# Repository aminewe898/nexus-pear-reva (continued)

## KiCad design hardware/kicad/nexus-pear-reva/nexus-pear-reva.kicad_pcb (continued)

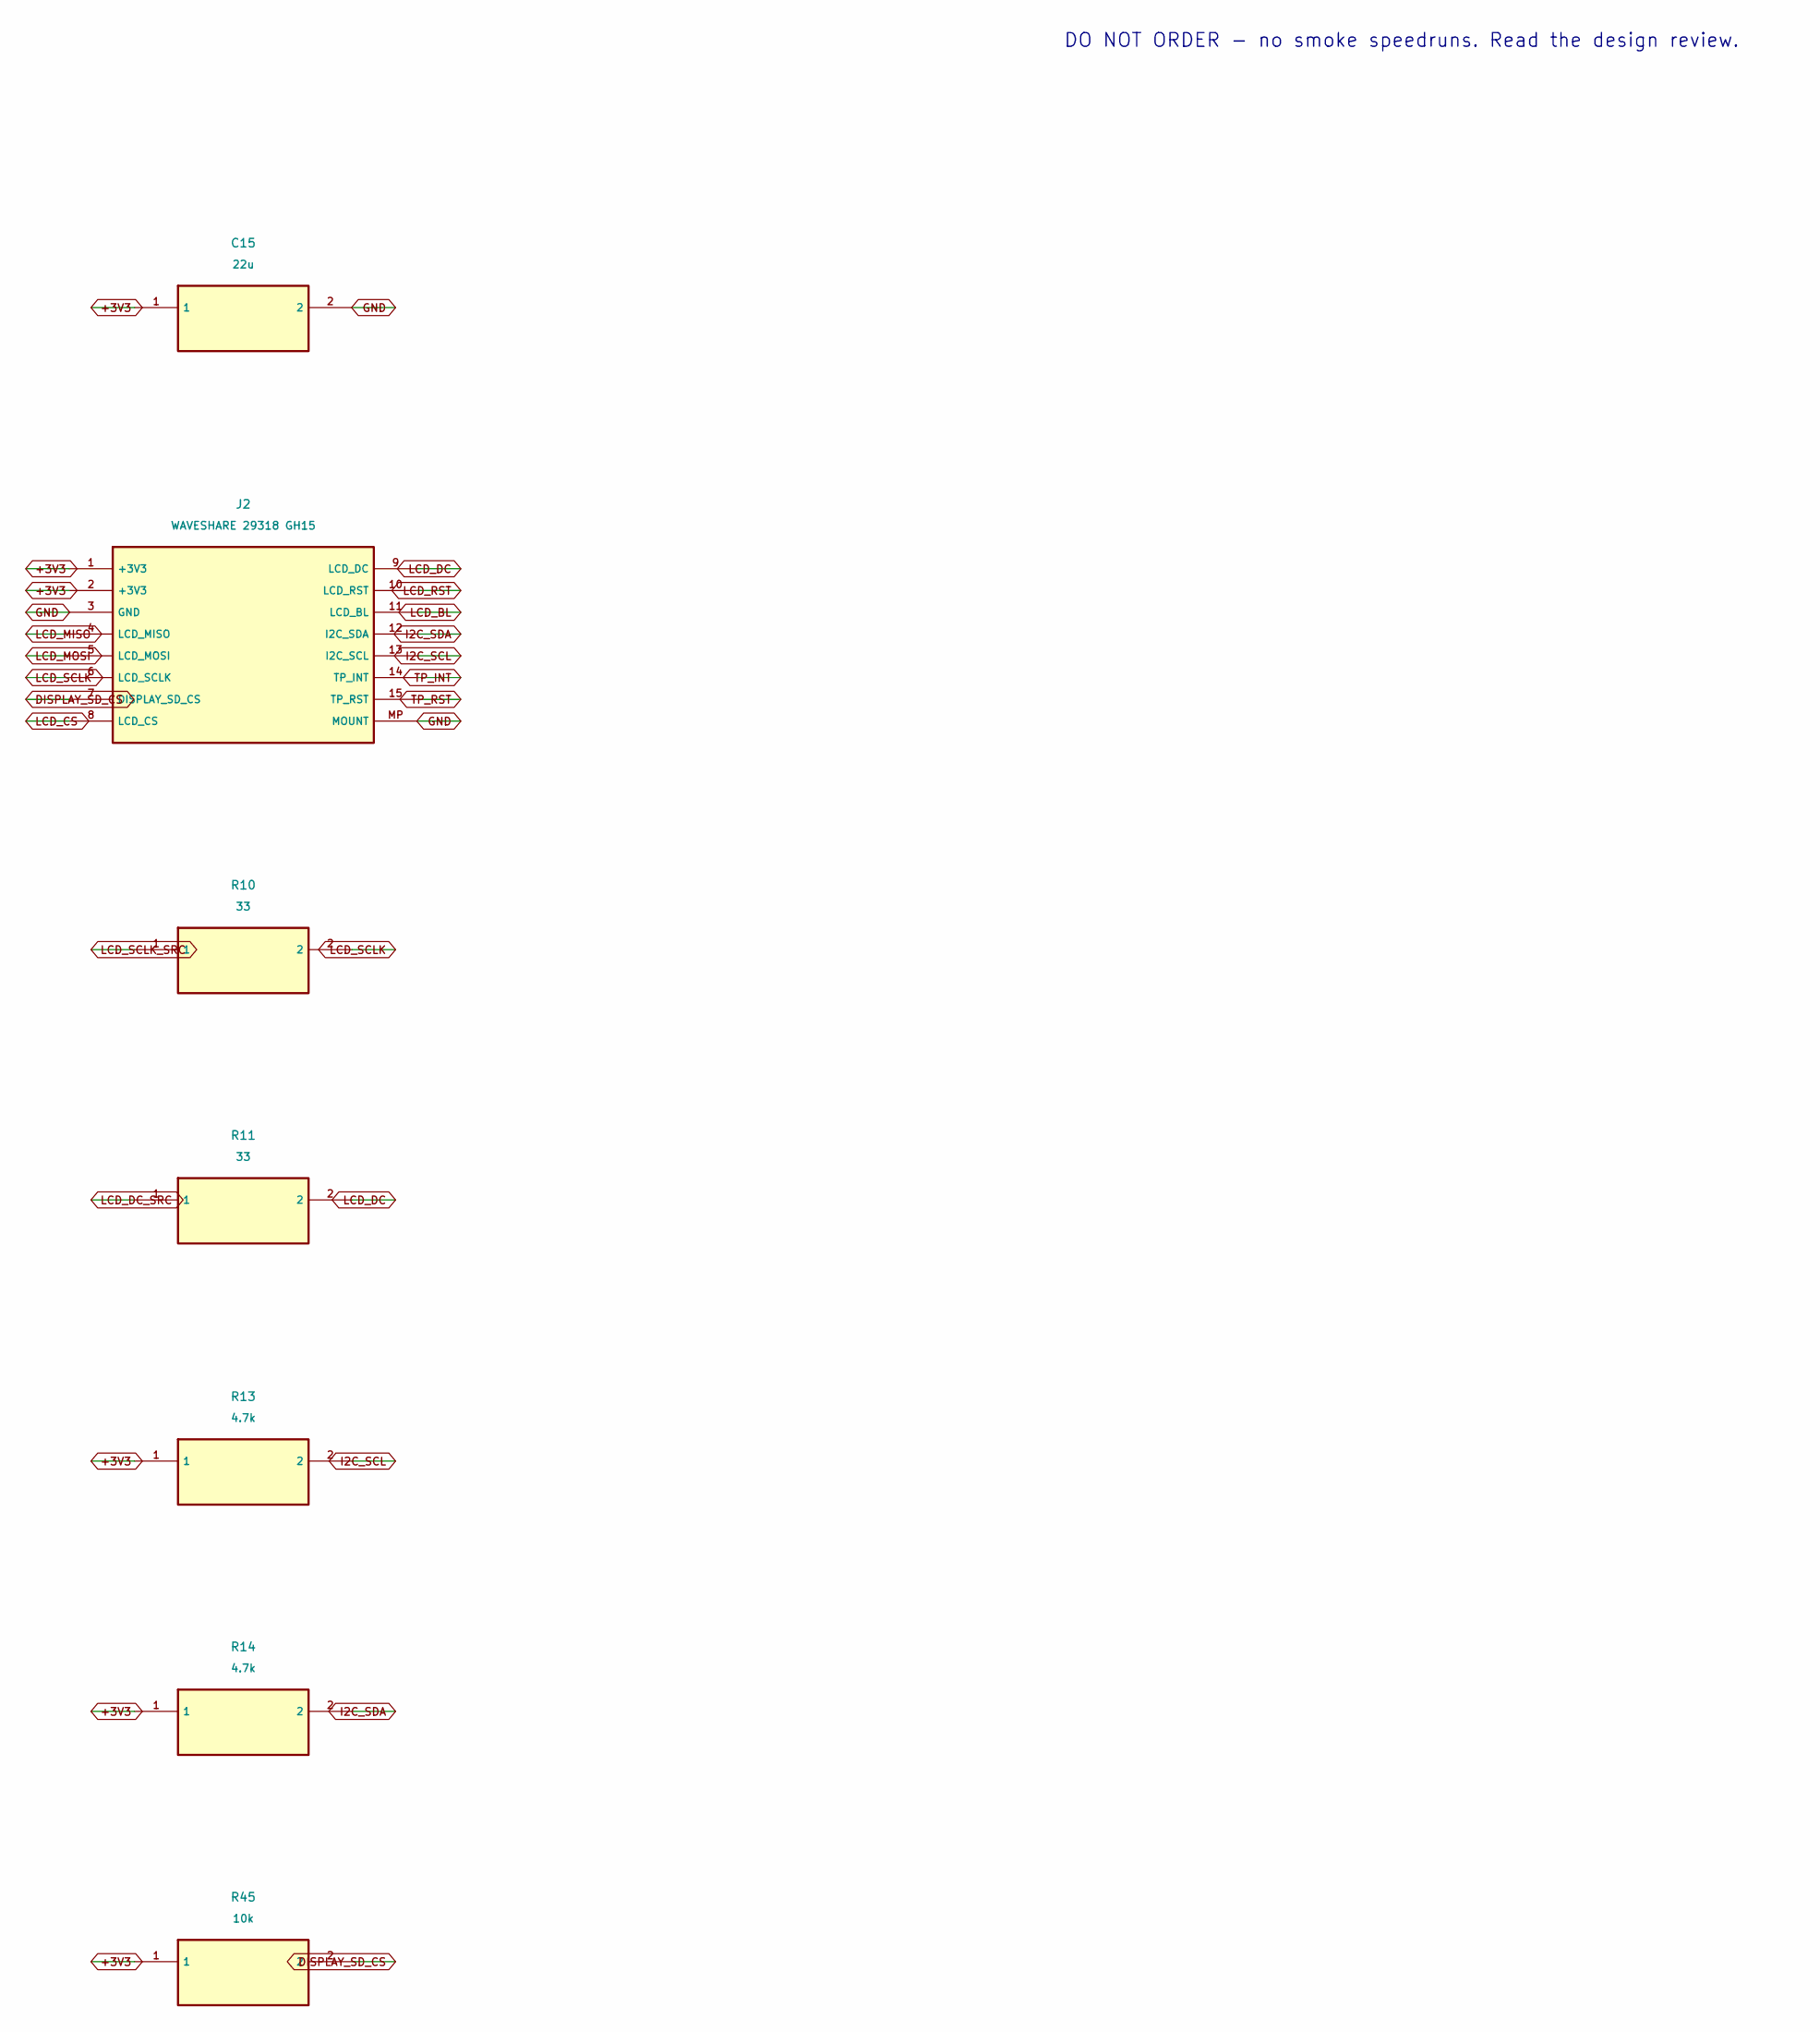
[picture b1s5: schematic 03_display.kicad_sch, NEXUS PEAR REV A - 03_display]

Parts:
C15: 22u; C_1206_3216Metric; MPN GRM31CR61A226KE19L
J2: WAVESHARE 29318 GH15; JST_GH_SM15B-GHS-TB_1x15-1MP_P1.25mm_Horizontal; MPN SM15B-GHS-TB(LF)(SN)
R10, R11: 33; R_0805_2012Metric; MPN RC0805FR-0733RL
R13, R14: 4.7k; R_0805_2012Metric; MPN RC0805FR-074K7L
R45: 10k; R_0805_2012Metric; MPN RC0805FR-0710KL

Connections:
+3V3: C15.1, J2.1 (+3V3), J2.2 (+3V3), R13.1, R14.1, R45.1; also elsewhere on the board
DISPLAY_SD_CS: J2.7 (DISPLAY_SD_CS), R45.2
GND: C15.2, J2.3 (GND), J2.MP (MOUNT); also elsewhere on the board
I2C_SCL: J2.13 (I2C_SCL), R13.2; also elsewhere on the board
I2C_SDA: J2.12 (I2C_SDA), R14.2; also elsewhere on the board
LCD_BL: J2.11 (LCD_BL); also elsewhere on the board
LCD_CS: J2.8 (LCD_CS); also elsewhere on the board
LCD_DC: J2.9 (LCD_DC), R11.2
LCD_DC_SRC: R11.1; also elsewhere on the board
LCD_MISO: J2.4 (LCD_MISO); also elsewhere on the board
LCD_MOSI: J2.5 (LCD_MOSI); also elsewhere on the board
LCD_RST: J2.10 (LCD_RST); also elsewhere on the board
LCD_SCLK: J2.6 (LCD_SCLK), R10.2
LCD_SCLK_SRC: R10.1; also elsewhere on the board
TP_INT: J2.14 (TP_INT); also elsewhere on the board
TP_RST: J2.15 (TP_RST); also elsewhere on the board

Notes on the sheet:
DO NOT ORDER - no smoke speedruns. Read the design review.

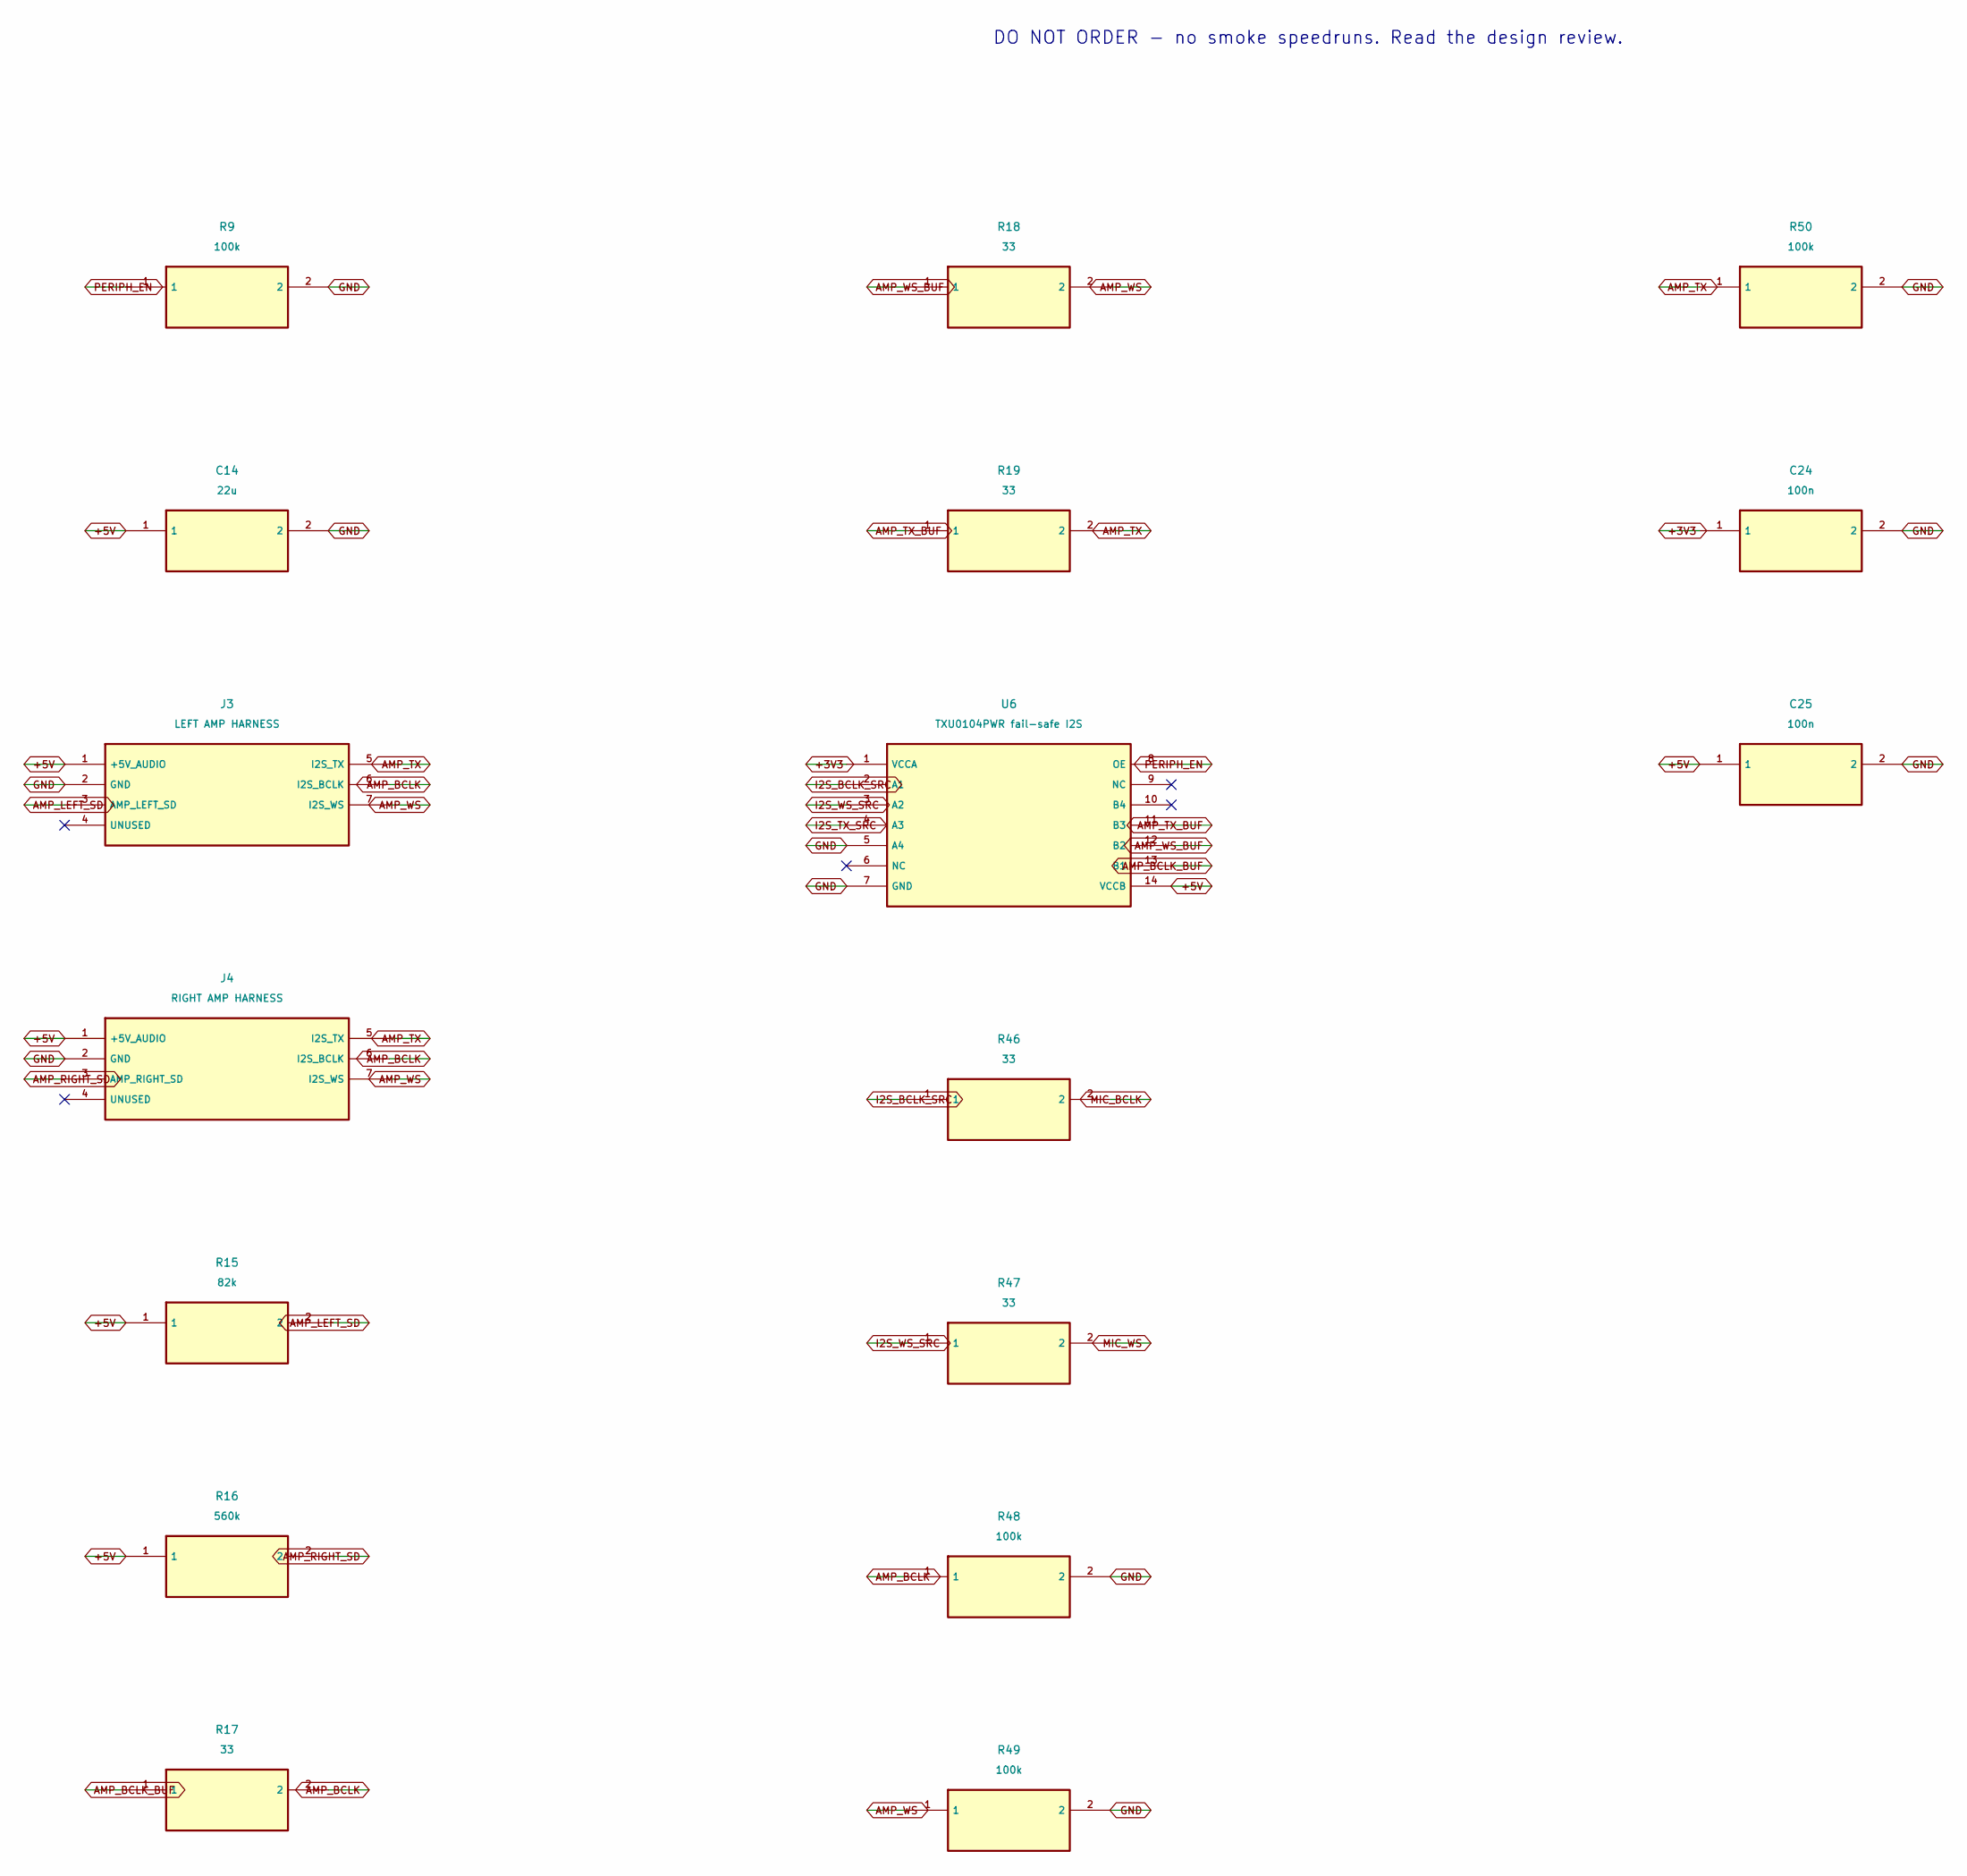
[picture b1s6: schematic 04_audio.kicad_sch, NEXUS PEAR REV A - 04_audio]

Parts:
C14: 22u; C_1206_3216Metric; MPN GRM31CR61A226KE19L
C24, C25: 100n; C_0805_2012Metric; MPN GRM21BR71H104KA01L
J3: LEFT AMP HARNESS; PinHeader_1x07_P2.54mm_Vertical; MPN TSW-007-07-G-S
J4: RIGHT AMP HARNESS; PinHeader_1x07_P2.54mm_Vertical; MPN TSW-007-07-G-S
R9, R48, R49, R50: 100k; R_0805_2012Metric; MPN RC0805FR-07100KL
R15: 82k; R_0805_2012Metric; MPN RC0805FR-0782KL
R16: 560k; R_0805_2012Metric; MPN RC0805FR-07560KL
R17, R18, R19, R46, R47: 33; R_0805_2012Metric; MPN RC0805FR-0733RL
U6: TXU0104PWR fail-safe I2S; TSSOP-14_4.4x5mm_P0.65mm; MPN TXU0104PWR

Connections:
+3V3: C24.1, U6.1 (VCCA); also elsewhere on the board
+5V: C14.1, C25.1, J3.1 (+5V_AUDIO), J4.1 (+5V_AUDIO), R15.1, R16.1, U6.14 (VCCB); also elsewhere on the board
AMP_BCLK: J3.6 (I2S_BCLK), J4.6 (I2S_BCLK), R17.2, R48.1
AMP_BCLK_BUF: R17.1, U6.13 (B1)
AMP_LEFT_SD: J3.3 (AMP_LEFT_SD), R15.2
AMP_RIGHT_SD: J4.3 (AMP_RIGHT_SD), R16.2
AMP_TX: J3.5 (I2S_TX), J4.5 (I2S_TX), R19.2, R50.1
AMP_TX_BUF: R19.1, U6.11 (B3)
AMP_WS: J3.7 (I2S_WS), J4.7 (I2S_WS), R18.2, R49.1
AMP_WS_BUF: R18.1, U6.12 (B2)
GND: C14.2, C24.2, C25.2, J3.2 (GND), J4.2 (GND), R9.2, R48.2, R49.2, R50.2, U6.5 (A4), U6.7 (GND); also elsewhere on the board
I2S_BCLK_SRC: R46.1, U6.2 (A1); also elsewhere on the board
I2S_TX_SRC: U6.4 (A3); also elsewhere on the board
I2S_WS_SRC: R47.1, U6.3 (A2); also elsewhere on the board
MIC_BCLK: R46.2; also elsewhere on the board
MIC_WS: R47.2; also elsewhere on the board
PERIPH_EN: R9.1, U6.8 (OE); also elsewhere on the board

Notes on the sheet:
DO NOT ORDER - no smoke speedruns. Read the design review.

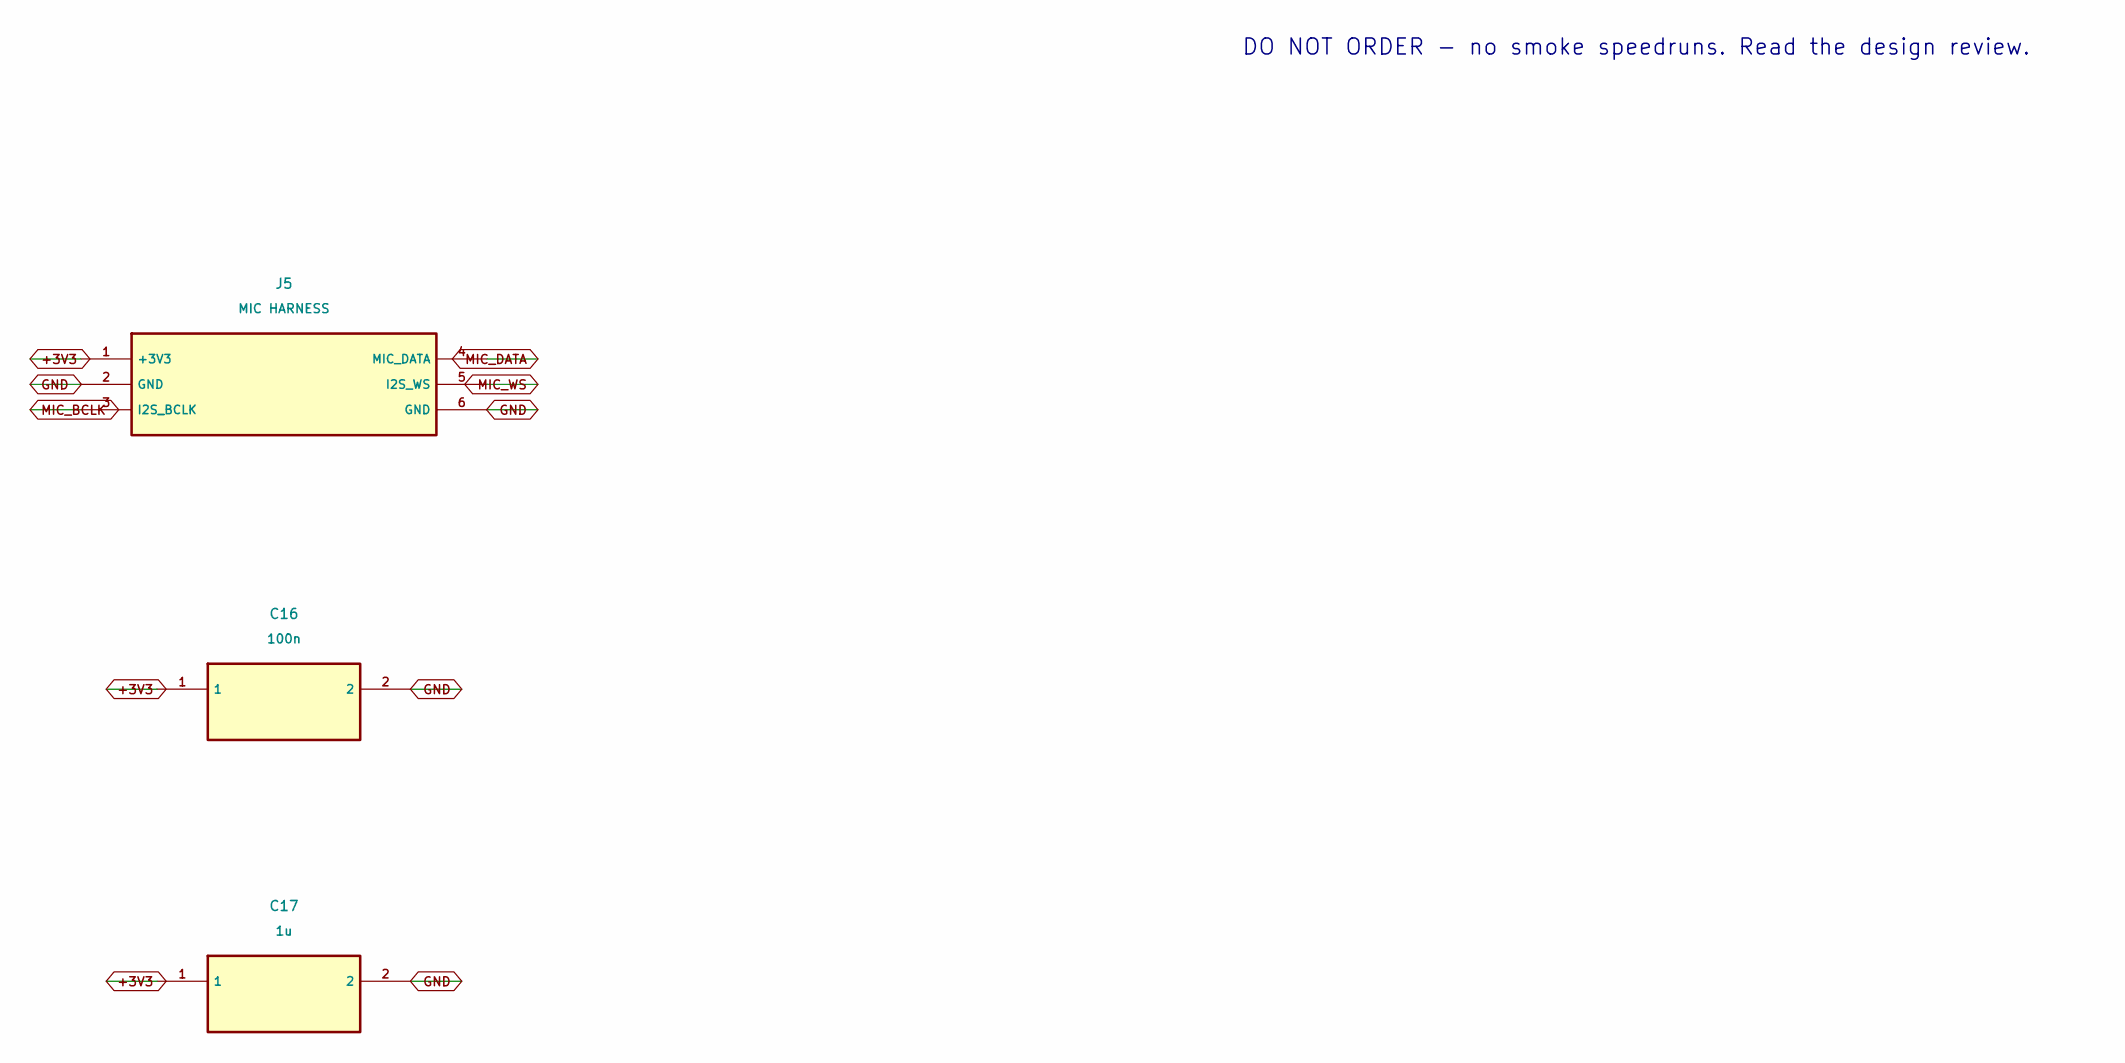
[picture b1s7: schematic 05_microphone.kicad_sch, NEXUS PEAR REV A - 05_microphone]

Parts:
C16: 100n; C_0805_2012Metric; MPN GRM21BR71H104KA01L
C17: 1u; C_0805_2012Metric; MPN GRM21BR71A105KA01L
J5: MIC HARNESS; PinHeader_1x06_P2.54mm_Vertical; MPN TSW-006-07-G-S

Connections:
+3V3: C16.1, C17.1, J5.1 (+3V3); also elsewhere on the board
GND: C16.2, C17.2, J5.2 (GND), J5.6 (GND); also elsewhere on the board
MIC_BCLK: J5.3 (I2S_BCLK); also elsewhere on the board
MIC_DATA: J5.4 (MIC_DATA); also elsewhere on the board
MIC_WS: J5.5 (I2S_WS); also elsewhere on the board

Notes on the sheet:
DO NOT ORDER - no smoke speedruns. Read the design review.

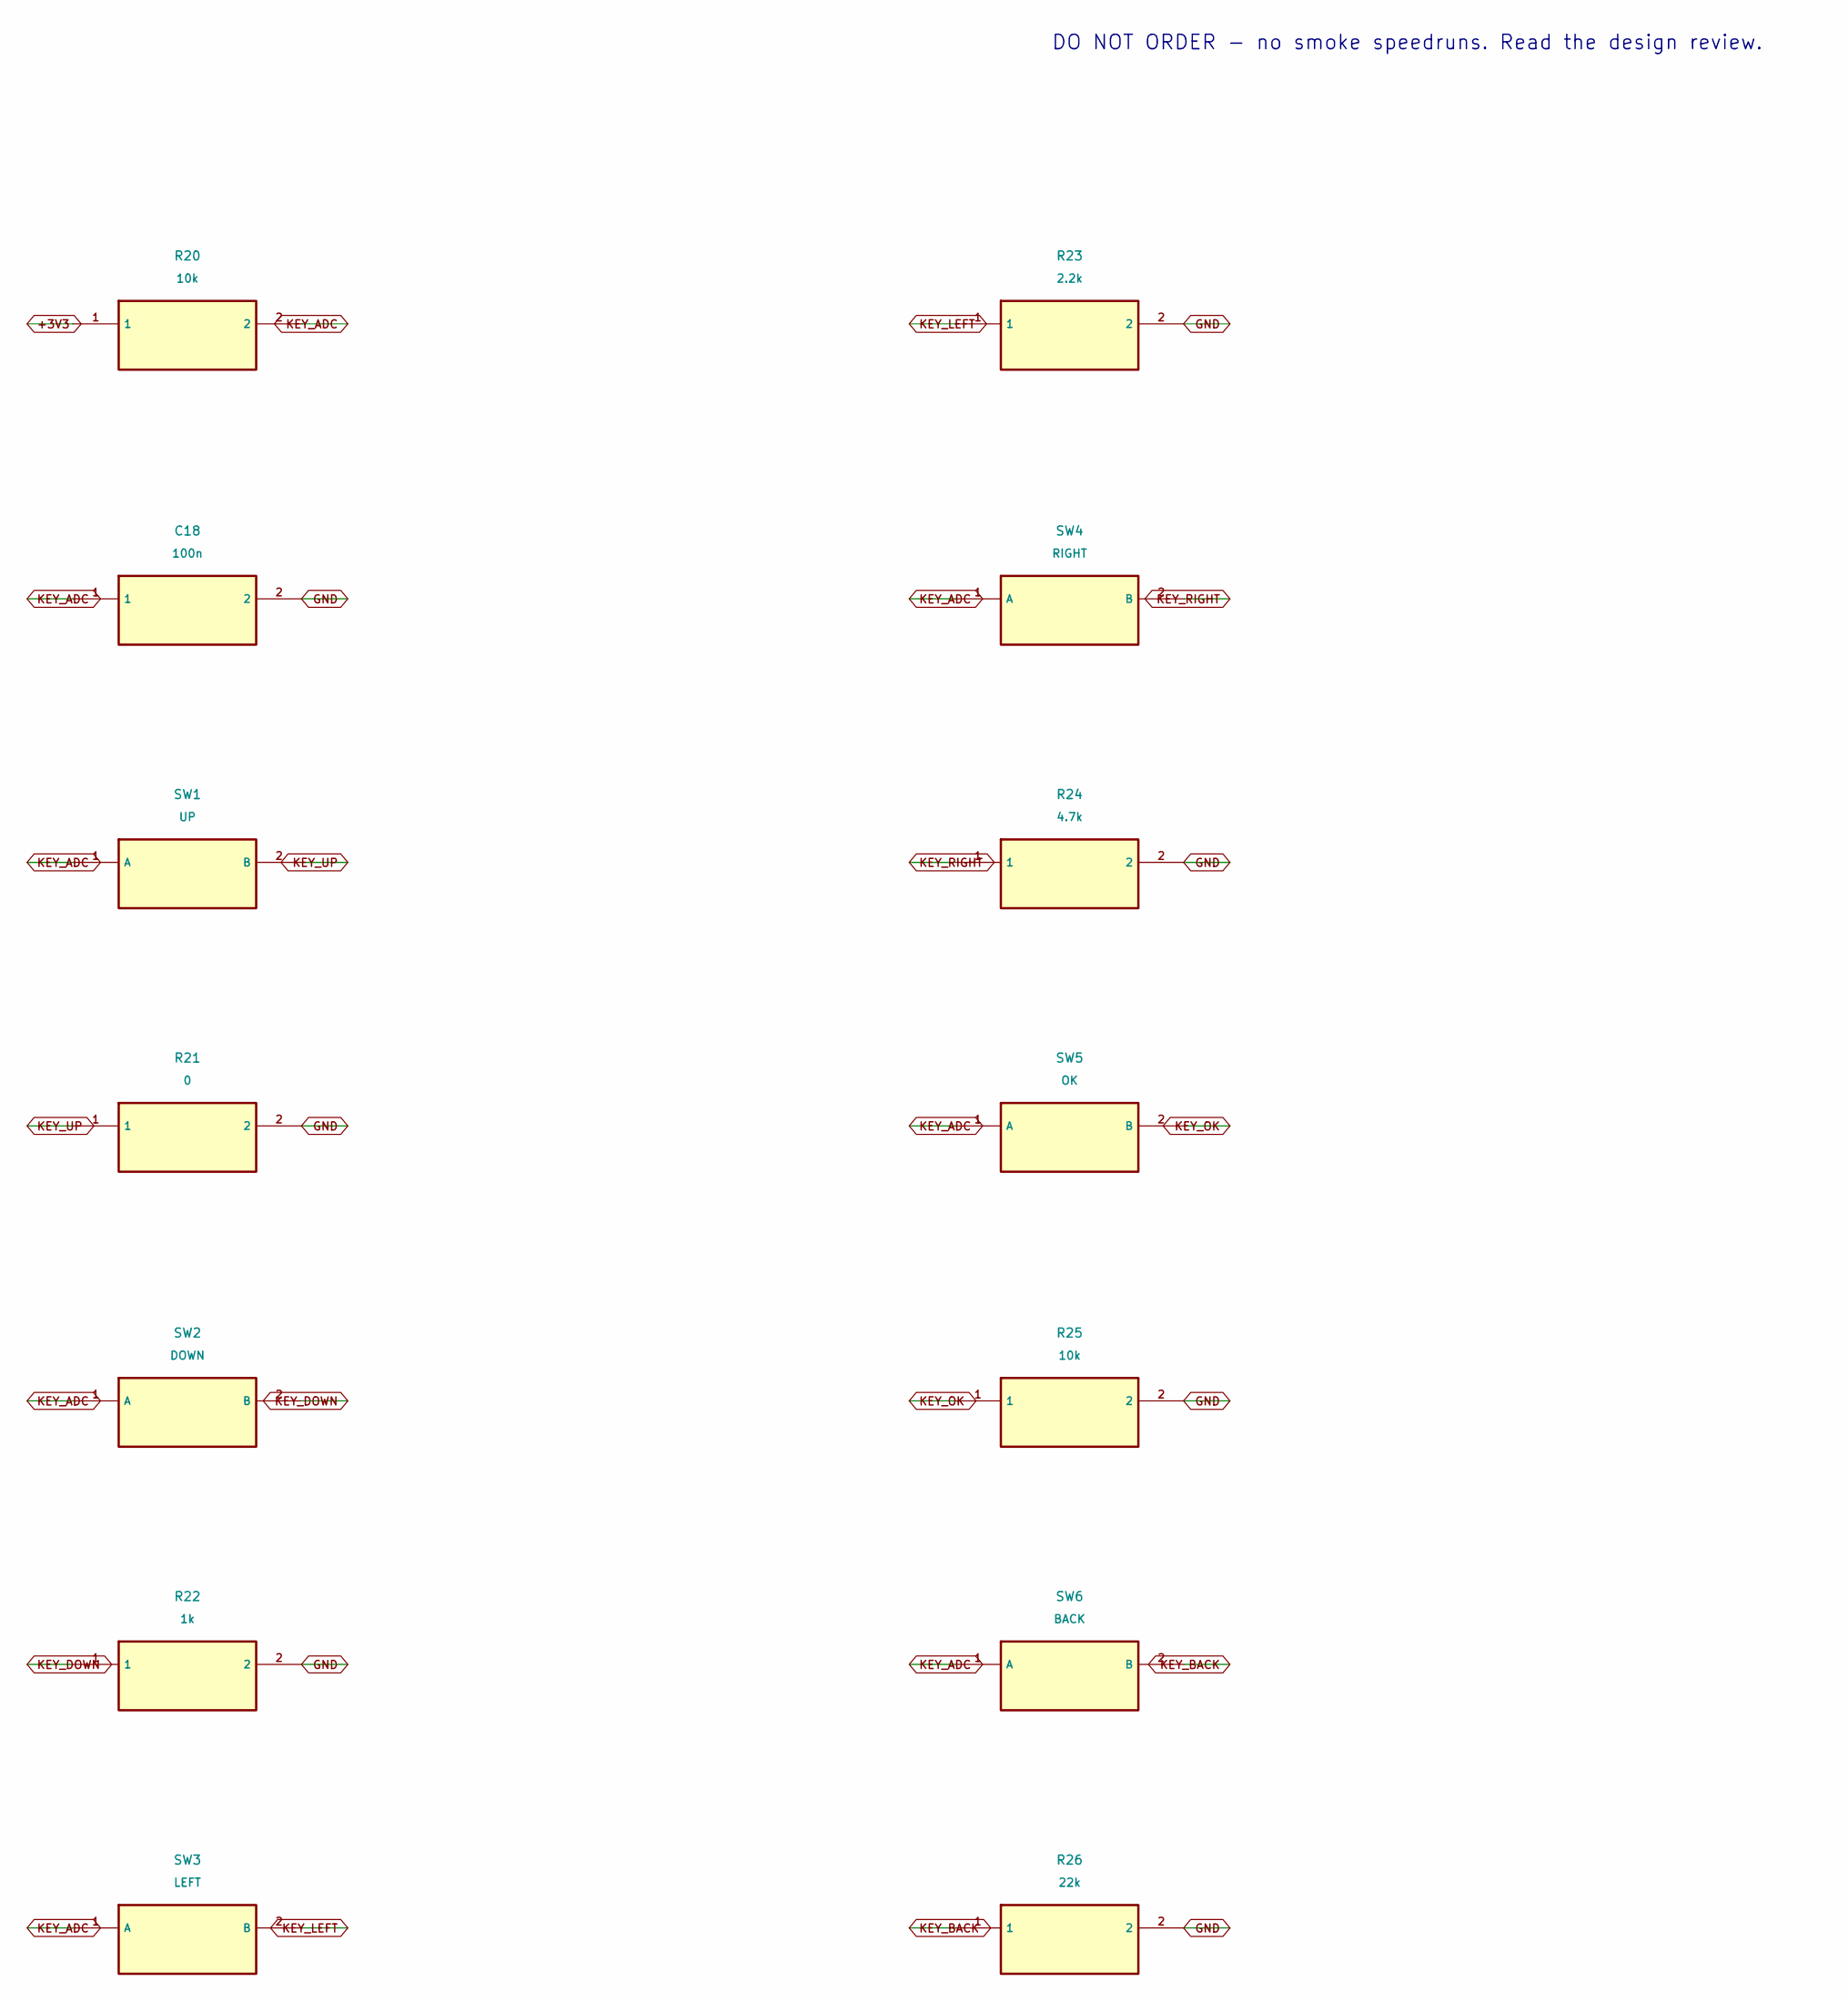
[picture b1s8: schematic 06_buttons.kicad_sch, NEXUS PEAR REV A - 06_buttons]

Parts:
C18: 100n; C_0805_2012Metric; MPN GRM21BR71H104KA01L
R20, R25: 10k; R_0805_2012Metric; MPN RC0805FR-0710KL
R21: 0; R_0805_2012Metric; MPN RC0805JR-070RL
R22: 1k; R_0805_2012Metric; MPN RC0805FR-071KL
R23: 2.2k; R_0805_2012Metric; MPN RC0805FR-072K2L
R24: 4.7k; R_0805_2012Metric; MPN RC0805FR-074K7L
R26: 22k; R_0805_2012Metric; MPN RC0805FR-0722KL
SW1: UP; SW_PUSH_6mm; MPN B3F-1000
SW2: DOWN; SW_PUSH_6mm; MPN B3F-1000
SW3: LEFT; SW_PUSH_6mm; MPN B3F-1000
SW4: RIGHT; SW_PUSH_6mm; MPN B3F-1000
SW5: OK; SW_PUSH_6mm; MPN B3F-1000
SW6: BACK; SW_PUSH_6mm; MPN B3F-1000

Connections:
+3V3: R20.1; also elsewhere on the board
GND: C18.2, R21.2, R22.2, R23.2, R24.2, R25.2, R26.2; also elsewhere on the board
KEY_ADC: C18.1, R20.2, SW1.1 (A), SW2.1 (A), SW3.1 (A), SW4.1 (A), SW5.1 (A), SW6.1 (A); also elsewhere on the board
KEY_BACK: R26.1, SW6.2 (B)
KEY_DOWN: R22.1, SW2.2 (B)
KEY_LEFT: R23.1, SW3.2 (B)
KEY_OK: R25.1, SW5.2 (B)
KEY_RIGHT: R24.1, SW4.2 (B)
KEY_UP: R21.1, SW1.2 (B)

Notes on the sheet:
DO NOT ORDER - no smoke speedruns. Read the design review.

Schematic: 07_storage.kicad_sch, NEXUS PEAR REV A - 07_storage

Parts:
C19: 22u; C_1206_3216Metric; MPN GRM31CR61A226KE19L
J6: 3V3 SD HARNESS; PinHeader_1x06_P2.54mm_Vertical; MPN TSW-006-07-G-S
R27, R28: 33; R_0805_2012Metric; MPN RC0805FR-0733RL
R29, R30: 10k; R_0805_2012Metric; MPN RC0805FR-0710KL

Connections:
+3V3: C19.1, J6.1 (+3V3), R29.1, R30.1; also elsewhere on the board
GND: C19.2, J6.2 (GND); also elsewhere on the board
SD_CS: J6.6 (SD_CS), R29.2; also elsewhere on the board
SD_MISO: J6.5 (SD_MISO), R30.2; also elsewhere on the board
SD_MOSI: J6.4 (SD_MOSI), R28.2
SD_MOSI_SRC: R28.1; also elsewhere on the board
SD_SCK: J6.3 (SD_SCK), R27.2; also elsewhere on the board
SD_SCK_SRC: R27.1; also elsewhere on the board

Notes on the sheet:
DO NOT ORDER - no smoke speedruns. Read the design review.

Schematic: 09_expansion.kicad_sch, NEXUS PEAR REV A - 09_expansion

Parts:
J8: I2C EXPANSION; PinHeader_1x04_P2.54mm_Vertical; MPN TSW-004-07-G-S

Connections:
+3V3: J8.1 (+3V3); also elsewhere on the board
GND: J8.2 (GND); also elsewhere on the board
I2C_SCL: J8.3 (I2C_SCL); also elsewhere on the board
I2C_SDA: J8.4 (I2C_SDA); also elsewhere on the board

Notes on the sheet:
DO NOT ORDER - no smoke speedruns. Read the design review.

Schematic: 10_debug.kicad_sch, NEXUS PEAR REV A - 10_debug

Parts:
D1: STATUS amber; LED_0805_2012Metric; MPN LTST-C170KFKT
H1, H2, H3, H4: M3 mounting; MountingHole_3.2mm_M3; MPN NPTH 3.2mm
J7: UART RECOVERY; PinHeader_1x06_P2.54mm_Vertical; MPN TSW-006-07-G-S
R31: 1k; R_0805_2012Metric; MPN RC0805FR-071KL
SW7: BOOT; SW_PUSH_6mm; MPN B3F-1000
SW8: RESET; SW_PUSH_6mm; MPN B3F-1000
TP1: VBUS; TestPoint_Pad_D2.0mm; MPN PCB TEST PAD
TP2, TP8: +5V; TestPoint_Pad_D2.0mm; MPN PCB TEST PAD
TP3, TP7: +3V3; TestPoint_Pad_D2.0mm; MPN PCB TEST PAD
TP4: GND; TestPoint_Pad_D2.0mm; MPN PCB TEST PAD
TP5: EN; TestPoint_Pad_D2.0mm; MPN PCB TEST PAD
TP6: BOOT; TestPoint_Pad_D2.0mm; MPN PCB TEST PAD
TP9: I2C_SCL; TestPoint_Pad_D2.0mm; MPN PCB TEST PAD
TP10: I2C_SDA; TestPoint_Pad_D2.0mm; MPN PCB TEST PAD
TP11: MIC_BCLK; TestPoint_Pad_D2.0mm; MPN PCB TEST PAD
TP12: MIC_WS; TestPoint_Pad_D2.0mm; MPN PCB TEST PAD
TP13: MIC_DATA; TestPoint_Pad_D2.0mm; MPN PCB TEST PAD
TP14: SD_SCK; TestPoint_Pad_D2.0mm; MPN PCB TEST PAD
TP15: PERIPH_EN; TestPoint_Pad_D2.0mm; MPN PCB TEST PAD
TP16: CC_3A_OK; TestPoint_Pad_D2.0mm; MPN PCB TEST PAD
TP17: IMON; TestPoint_Pad_D2.0mm; MPN PCB TEST PAD

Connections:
+3V3: J7.6 (+3V3), TP3.1, TP7.1; also elsewhere on the board
+5V: TP2.1, TP8.1; also elsewhere on the board
BOOT: J7.5 (BOOT), SW7.1 (A), TP6.1; also elsewhere on the board
CC_3A_OK: TP16.1; also elsewhere on the board
EN: J7.4 (EN), SW8.1 (A), TP5.1; also elsewhere on the board
GND: D1.1 (K), J7.1 (GND), SW7.2 (B), SW8.2 (B), TP4.1; also elsewhere on the board
I2C_SCL: TP9.1; also elsewhere on the board
I2C_SDA: TP10.1; also elsewhere on the board
IMON: TP17.1; also elsewhere on the board
LED_A: D1.2 (A), R31.2
MIC_BCLK: TP11.1; also elsewhere on the board
MIC_DATA: TP13.1; also elsewhere on the board
MIC_WS: TP12.1; also elsewhere on the board
PERIPH_EN: TP15.1; also elsewhere on the board
SD_SCK: TP14.1; also elsewhere on the board
STATUS: R31.1; also elsewhere on the board
UART_RX: J7.3 (UART_RX); also elsewhere on the board
UART_TX: J7.2 (UART_TX); also elsewhere on the board
VBUS: TP1.1; also elsewhere on the board

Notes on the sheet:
DO NOT ORDER - no smoke speedruns. Read the design review.
